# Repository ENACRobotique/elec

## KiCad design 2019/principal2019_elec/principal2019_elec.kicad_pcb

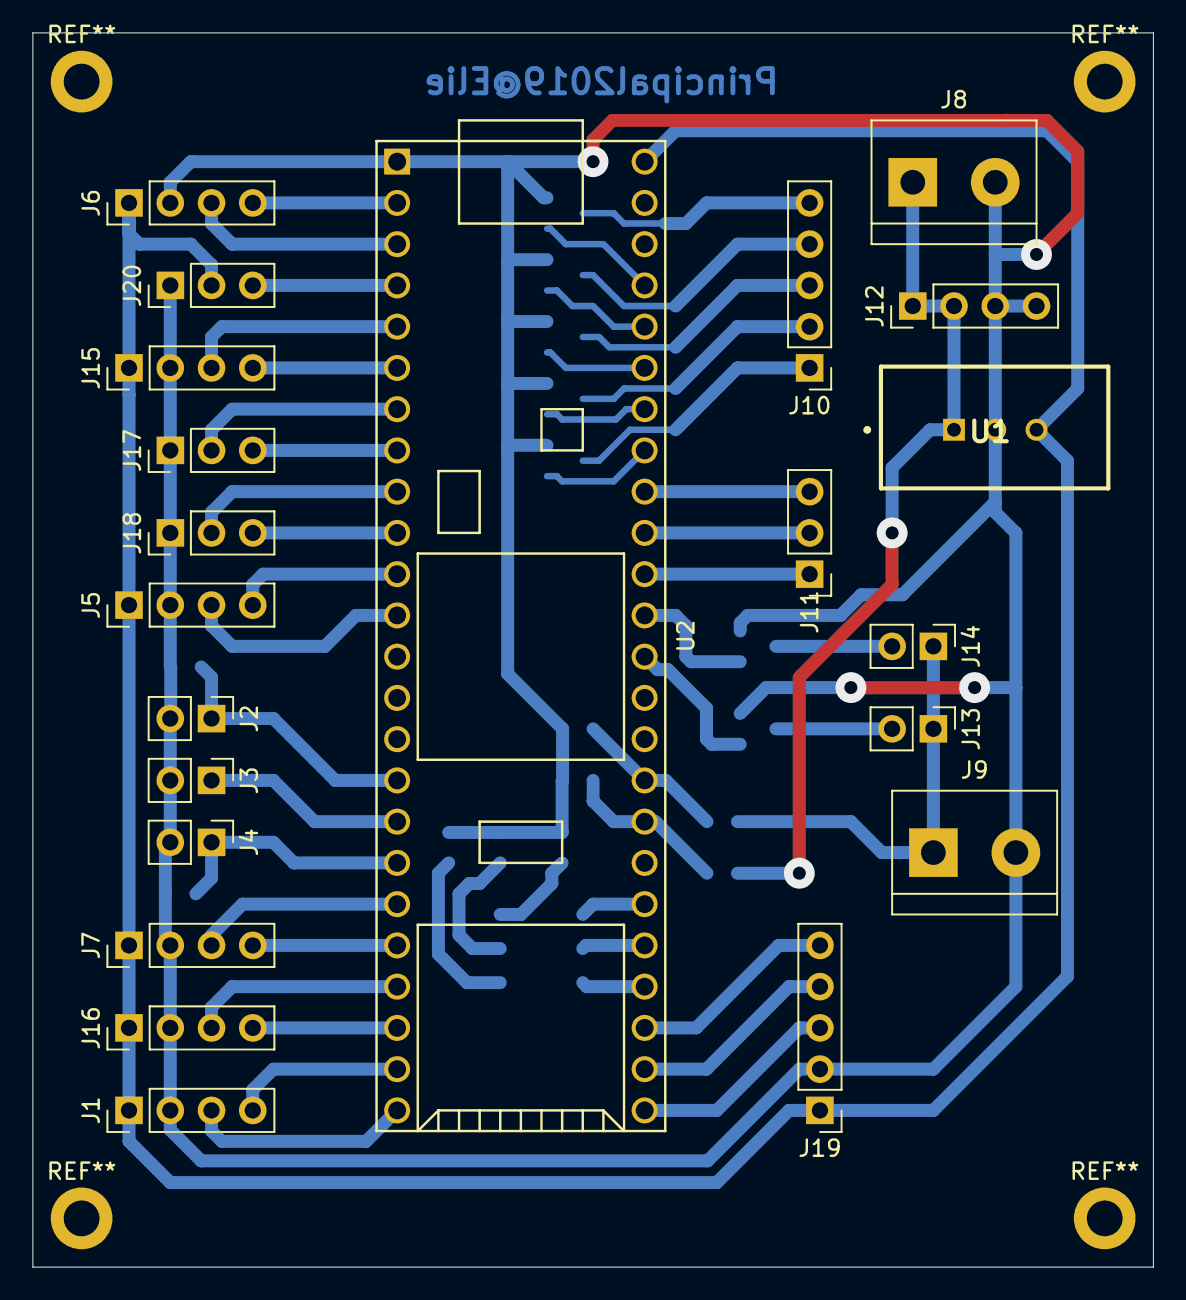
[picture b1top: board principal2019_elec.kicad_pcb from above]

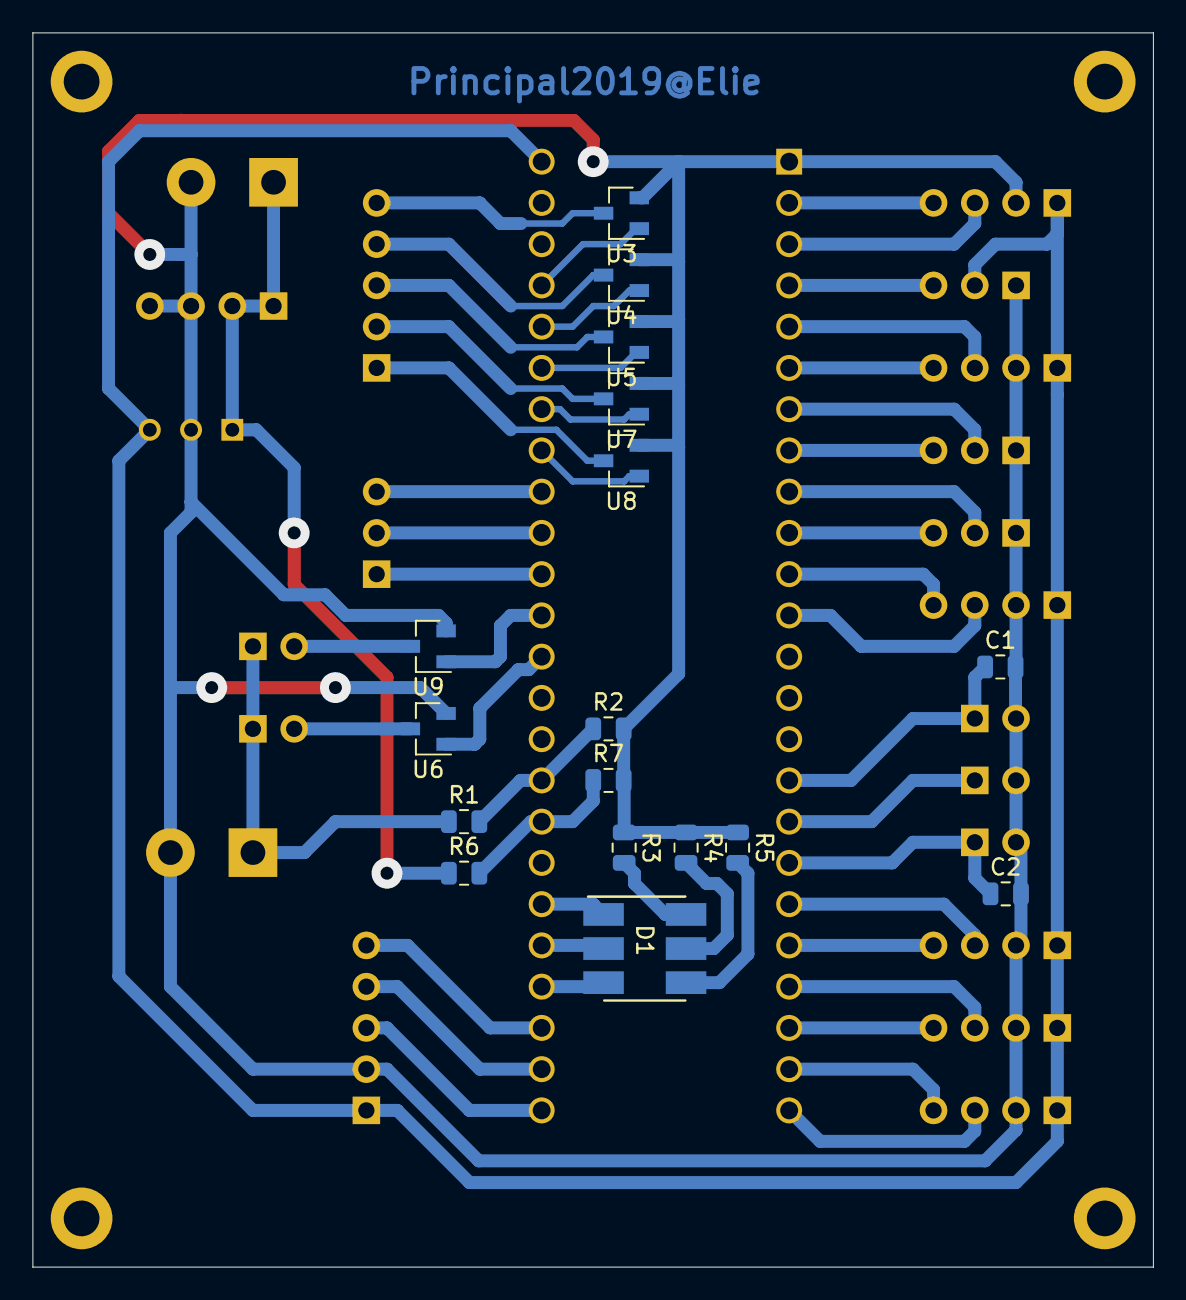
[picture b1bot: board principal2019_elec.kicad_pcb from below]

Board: 2 copper layers, 69.0 x 76.0 mm, 39 parts (17 on the bottom side), 52 nets.

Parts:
C1, C2: 100n; C_0805_2012Metric
D1: LED; PLCC6_CLP6C-FKB
J1: UART4; PinHeader_1x04_P2.54mm_Vertical
J2: tirette; PinHeader_1x02_P2.54mm_Vertical
J3: couleur; PinHeader_1x02_P2.54mm_Vertical
J4: selecteur; PinHeader_1x02_P2.54mm_Vertical
J5: UART2; PinHeader_1x04_P2.54mm_Vertical
J6: Raspi; PinHeader_1x04_P2.54mm_Vertical
J7: doigt_display; PinHeader_1x04_P2.54mm_Vertical
J8: conn_bat_sig; TerminalBlock_bornier-2_P5.08mm
J9: conn_bat_pow; TerminalBlock_bornier-2_P5.08mm
J10: Conn_01x05_Male; PinHeader_1x05_P2.54mm_Vertical
J11: lidar_out; PinHeader_1x03_P2.54mm_Vertical
J12: alim_lidar; PinHeader_1x04_P2.54mm_Vertical
J13: vanne; PinHeader_1x02_P2.54mm_Vertical
J14: pompe; PinHeader_1x02_P2.54mm_Vertical
J15: enc_mot1; PinHeader_1x04_P2.54mm_Vertical
J16: enc_mot2; PinHeader_1x04_P2.54mm_Vertical
J17: mot1; PinHeader_1x03_P2.54mm_Vertical
J18: mot2; PinHeader_1x03_P2.54mm_Vertical
J19: dynamixel; PinHeader_1x05_P2.54mm_Vertical
J20: Servo; PinHeader_1x03_P2.54mm_Vertical
R1, R6: 10k; R_0805_2012Metric
R2, R7: 2.2k; R_0805_2012Metric
R3: 68; R_0805_2012Metric
R4, R5: 10; R_0805_2012Metric
U1: regu_5V; TSR-2
U2: Teensy3.5; Teensy35_36
U3: mosfet_lid_I1; SOT-23
U4: mosfet_lid_I2; SOT-23
U5: mosfet_lid_I3; SOT-23
U6: mosfet_vanne; SOT-23
U7: mosfet_lid_I4; SOT-23
U8: mosfet_lid_I5; SOT-23
U9: mosfet_pompe; SOT-23

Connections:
+5V: J1.1, J5.1, J6.1, J7.1, J15.1, J16.1, J19.1, J20.2, U1.3, U2.53
+12P: J9.1, J13.1, J14.1, R1.1
+12V: J8.1, J12.1, J12.2, R6.1, U1.1
/CLK: J7.4, U2.20
/DIO: J7.3, U2.19
/RW_dyn: J19.5, U2.32
/Rx2: J5.4, U2.11
/Rx4: J1.4, U2.23
/Rx_dyn: J19.4, U2.31
/Rx_raspi: J6.4, U2.2
/Tx2: J5.3, U2.12
/Tx4: J1.3, U2.24
/Tx_dyn: J19.3, U2.30
/Tx_raspi: J6.3, U2.3
/Vpower: R1.2, R2.1, U2.38
/Vsignal: R6.2, R7.1, U2.37
/couleur: J3.1, U2.17
/enc1_A: J15.3, U2.5
/enc1_B: J15.4, U2.6
/enc2_A: J16.3, U2.21
/enc2_B: J16.4, U2.22
/led_B: D1.3, U2.33
/led_G: D1.2, U2.34
/led_R: D1.1, U2.35
/lidar_I1: U2.50, U3.1
/lidar_I2: U2.49, U4.1
/lidar_I3: U2.48, U5.1
/lidar_I4: U2.47, U7.1
/lidar_I5: U2.46, U8.1
/lidar_out1: J11.1, U2.43
/lidar_out2: J11.2, U2.44
/lidar_out3: J11.3, U2.45
/mot1_PWM: J17.2, U2.7
/mot1_dir: J17.3, U2.8
/mot2_PWM: J18.2, U2.9
/mot2_dir: J18.3, U2.10
/pompe: U2.42, U9.1
/selecteur: C2.1, J4.1, U2.18
/servo: J20.3, U2.4
/tirette: C1.1, J2.1, U2.16
/vanne: U2.41, U6.1
GND: C1.2, C2.2, J1.2, J2.2, J3.2, J4.2, J5.2, J6.2, J7.2, J8.2, J9.2, J12.3, J12.4, J15.2, J16.2, J17.1, J18.1, J19.2, J20.1, R2.2, R3.1, R4.1, R5.1, R7.2, U1.2, U2.1, U3.2, U4.2, U5.2, U6.2, U7.2, U8.2, U9.2
unnamed: D1.4, R5.2
unnamed: D1.5, R4.2
unnamed: D1.6, R3.2
unnamed: J10.1, U8.3
unnamed: J10.2, U7.3
unnamed: J10.3, U5.3
unnamed: J10.4, U4.3
unnamed: J10.5, U3.3
unnamed: J13.2, U6.3
unnamed: J14.2, U9.3

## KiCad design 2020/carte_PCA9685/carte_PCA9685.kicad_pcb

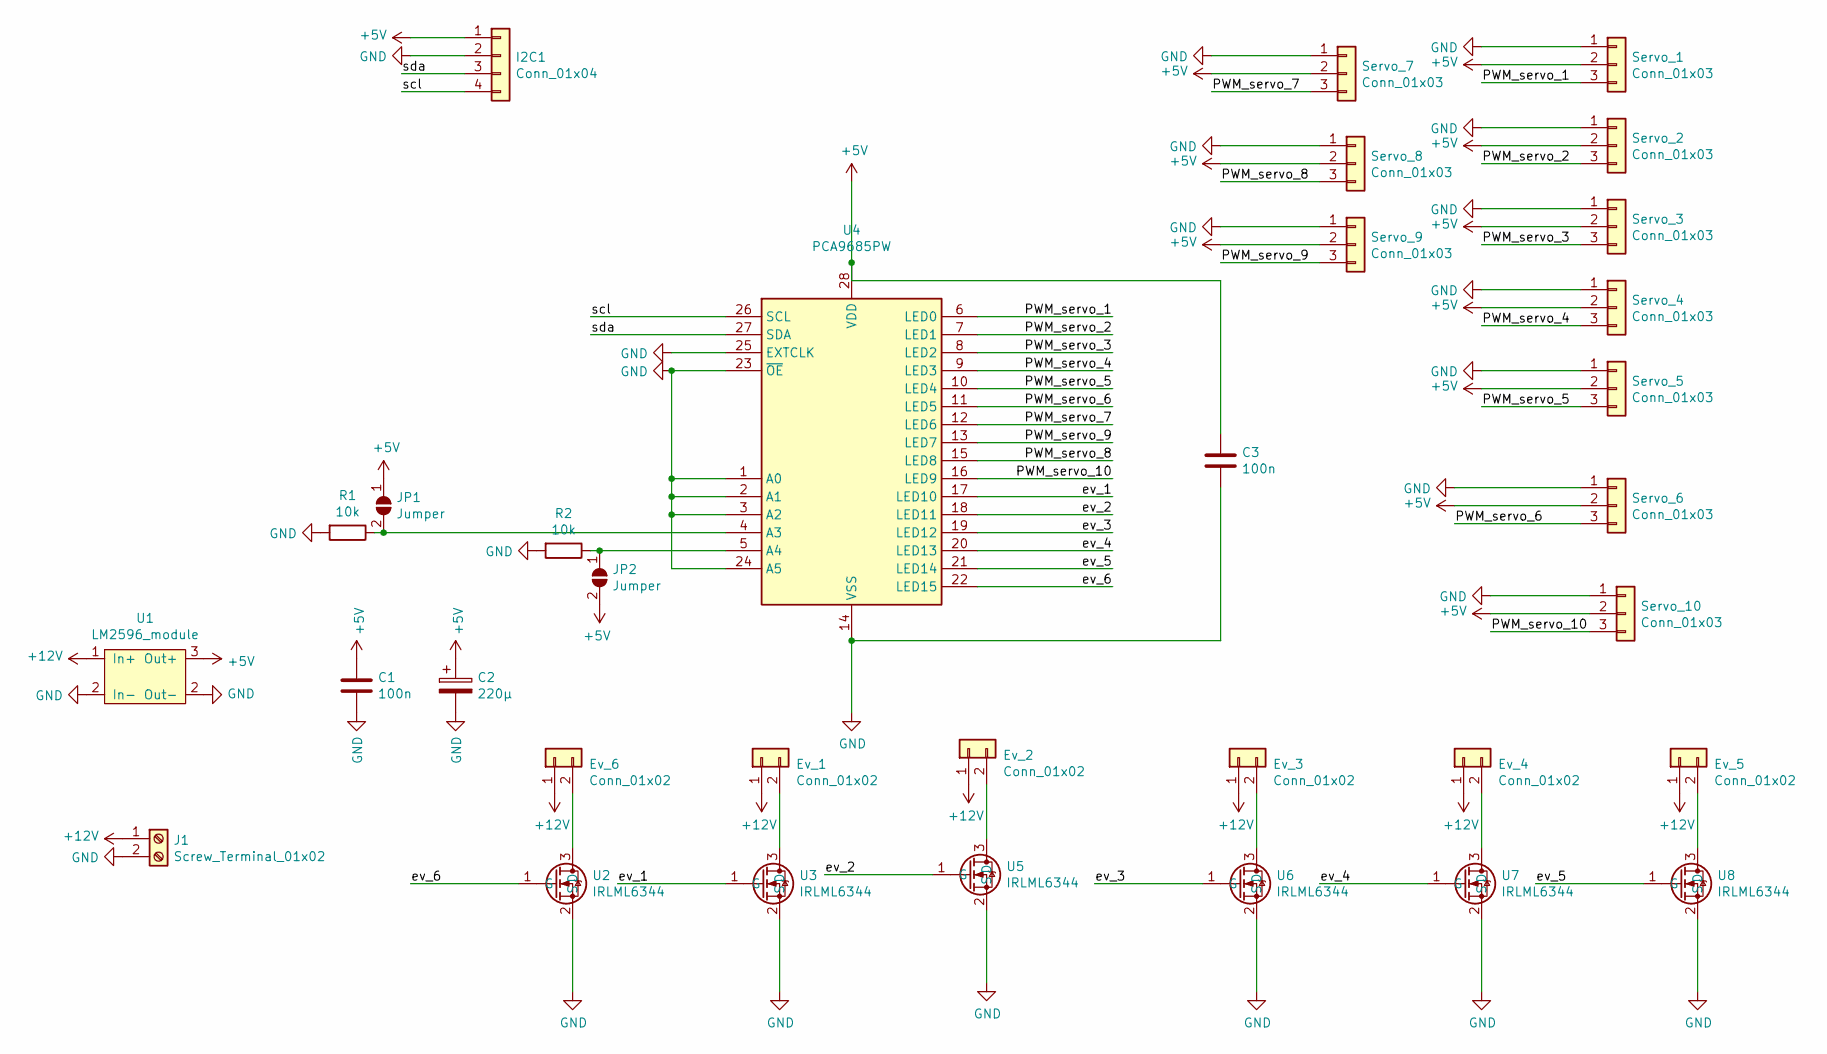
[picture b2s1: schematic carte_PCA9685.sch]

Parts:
C1, C3: 100n; C_0603_1608Metric_Pad1.05x0.95mm_HandSolder
C2: 220µ; CP_Radial_D10.0mm_P7.50mm
Ev_1, Ev_2, Ev_3, Ev_4, Ev_5, Ev_6: Conn_01x02; JST_XH_B2B-XH-A_1x02_P2.50mm_Vertical
I2C1: Conn_01x04; JST_XH_B4B-XH-A_1x04_P2.50mm_Vertical
J1: Screw_Terminal_01x02; TerminalBlock_4Ucon_1x02_P3.50mm_Vertical
JP1, JP2: Jumper; SolderJumper-2_P1.3mm_Open_TrianglePad1.0x1.5mm
R1, R2: 10k; R_0805_2012Metric
Servo_1, Servo_2, Servo_3, Servo_4, Servo_5, Servo_6, Servo_7, Servo_8, Servo_9, Servo_10: Conn_01x03; PinHeader_1x03_P2.54mm_Vertical
U1: LM2596_module
U2, U3, U5, U6, U7, U8: IRLML6344; SOT-23
U4: PCA9685PW; TSSOP-28_4.4x9.7mm_P0.65mm

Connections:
+5V: C1.2, C2.1, C3.1, I2C1.1, JP1.1 (A), JP2.2 (B), Servo_1.2, Servo_2.2, Servo_3.2, Servo_4.2, Servo_5.2, Servo_6.2, Servo_7.2, Servo_8.2, Servo_9.2, Servo_10.2, U1.3 (Out+), U4.28 (VDD)
+12V: Ev_1.1, Ev_2.1, Ev_3.1, Ev_4.1, Ev_5.1, Ev_6.1, J1.1, U1.1 (In+)
/PWM_servo_1: Servo_1.3, U4.6 (LED0)
/PWM_servo_2: Servo_2.3, U4.7 (LED1)
/PWM_servo_3: Servo_3.3, U4.8 (LED2)
/PWM_servo_4: Servo_4.3, U4.9 (LED3)
/PWM_servo_5: Servo_5.3, U4.10 (LED4)
/PWM_servo_6: Servo_6.3, U4.11 (LED5)
/PWM_servo_7: Servo_7.3, U4.12 (LED6)
/PWM_servo_8: Servo_8.3, U4.15 (LED8)
/PWM_servo_9: Servo_9.3, U4.13 (LED7)
/PWM_servo_10: Servo_10.3, U4.16 (LED9)
/ev_1: U3.1 (G), U4.17 (LED10)
/ev_2: U4.18 (LED11), U5.1 (G)
/ev_3: U4.19 (LED12), U6.1 (G)
/ev_4: U4.20 (LED13), U7.1 (G)
/ev_5: U4.21 (LED14), U8.1 (G)
/ev_6: U2.1 (G), U4.22 (LED15)
/scl: I2C1.4, U4.26 (SCL)
/sda: I2C1.3, U4.27 (SDA)
GND: C1.1, C2.2, C3.2, I2C1.2, J1.2, R1.2, R2.2, Servo_1.1, Servo_2.1, Servo_3.1, Servo_4.1, Servo_5.1, Servo_6.1, Servo_7.1, Servo_8.1, Servo_9.1, Servo_10.1, U1.2 (In-), U2.2 (S), U3.2 (S), U4.1 (A0), U4.2 (A1), U4.3 (A2), U4.14 (VSS), U4.23 (~OE), U4.24 (A5), U4.25 (EXTCLK), U5.2 (S), U6.2 (S), U7.2 (S), U8.2 (S)
unnamed: Ev_1.2, U3.3 (D)
unnamed: Ev_2.2, U5.3 (D)
unnamed: Ev_3.2, U6.3 (D)
unnamed: Ev_4.2, U7.3 (D)
unnamed: Ev_5.2, U8.3 (D)
unnamed: Ev_6.2, U2.3 (D)
unnamed: JP1.2 (B), R1.1, U4.4 (A3)
unnamed: JP2.1 (A), R2.1, U4.5 (A4)

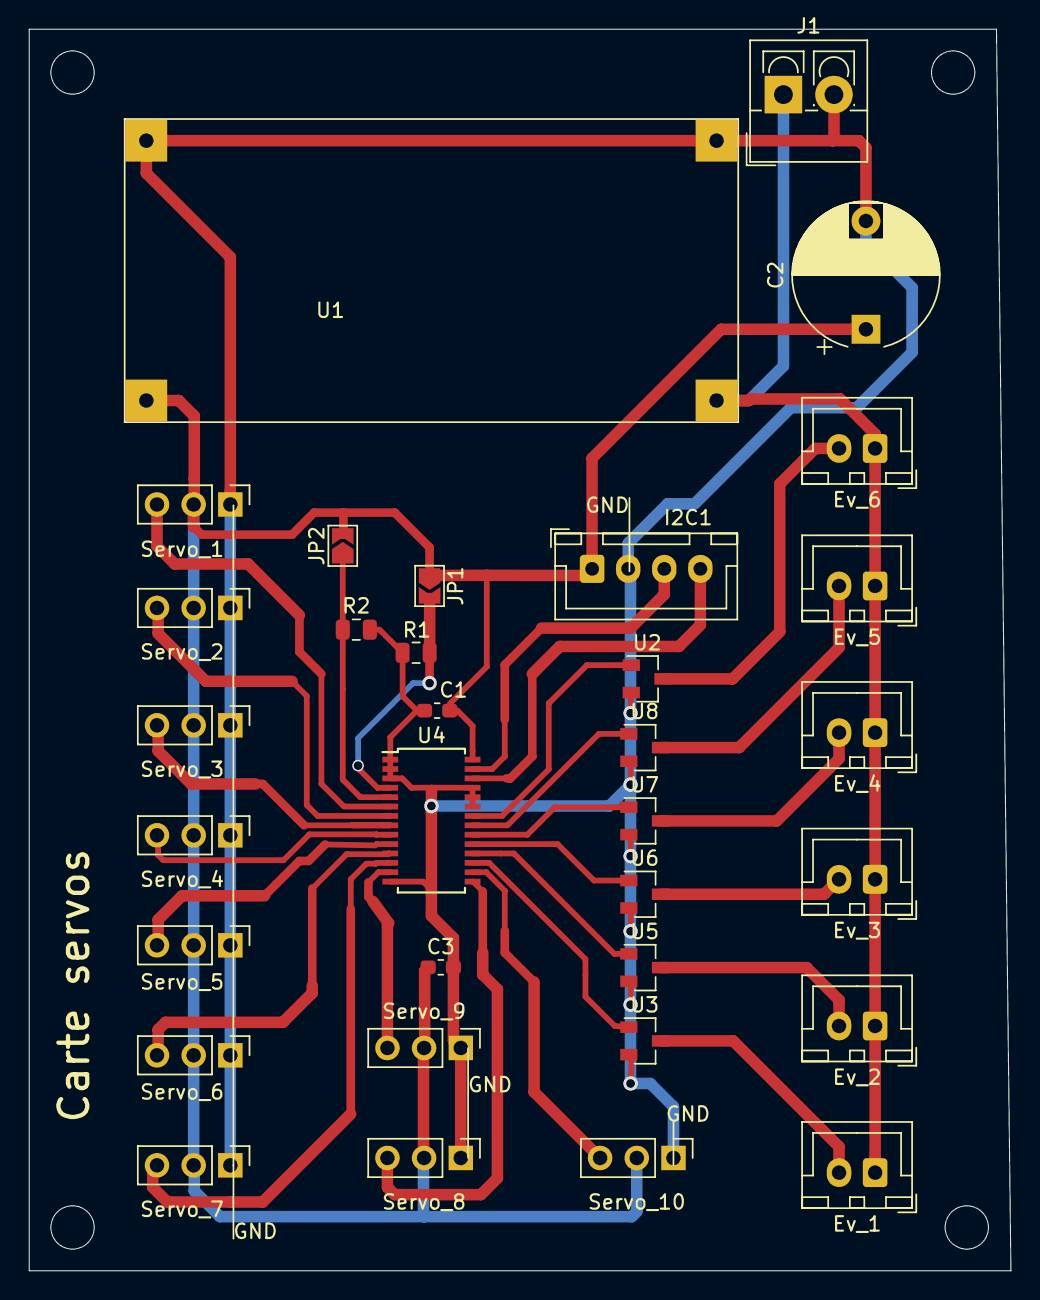
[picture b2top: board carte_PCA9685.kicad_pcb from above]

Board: 2 copper layers, 68.0 x 86.0 mm, 37 parts (0 on the bottom side), 29 nets.

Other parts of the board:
 : MountingHole_3mm
 #2,  #3,  #4: MountingHole_3mm

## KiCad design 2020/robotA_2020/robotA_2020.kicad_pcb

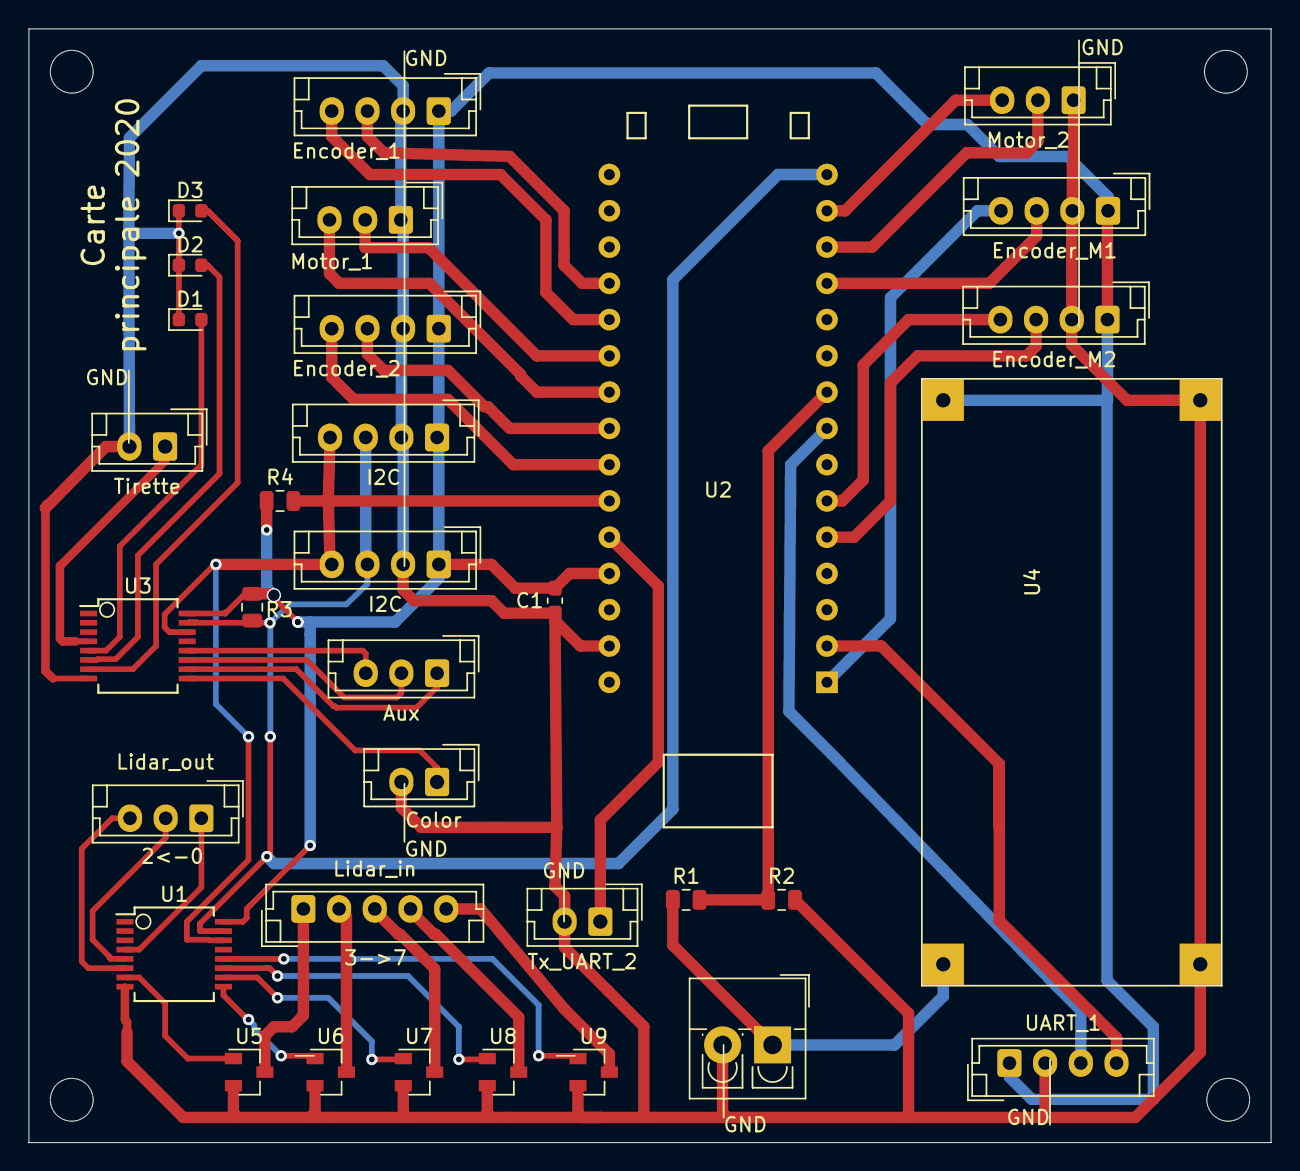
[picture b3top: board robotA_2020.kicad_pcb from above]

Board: 2 copper layers, 87.0 x 78.0 mm, 37 parts (0 on the bottom side), 42 nets.

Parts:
 : Screw_Terminal_01x02; TerminalBlock_4Ucon_1x02_P3.50mm_Vertical
 #2,  #3,  #4,  #5: MountingHole_3mm
Aux: Conn_01x03; JST_EH_B3B-EH-A_1x03_P2.50mm_Vertical
C1: 100nF; C_0603_1608Metric_Pad1.05x0.95mm_HandSolder
Color: Conn_01x02; JST_EH_B2B-EH-A_1x02_P2.50mm_Vertical
D1, D2, D3: LED; LED_0603_1608Metric
Encoder_1: Encoder_1; JST_EH_B4B-EH-A_1x04_P2.50mm_Vertical
Encoder_2: Encoder_2; JST_EH_B4B-EH-A_1x04_P2.50mm_Vertical
Encoder_M1: Encoder_M1; JST_EH_B4B-EH-A_1x04_P2.50mm_Vertical
Encoder_M2: Encoder_M2; JST_EH_B4B-EH-A_1x04_P2.50mm_Vertical
I2C, I2C#2: I2C_3; JST_EH_B4B-EH-A_1x04_P2.50mm_Vertical
Lidar_in: Conn_01x05; JST_EH_B5B-EH-A_1x05_P2.50mm_Vertical
Lidar_out: Conn_01x03; JST_EH_B3B-EH-A_1x03_P2.50mm_Vertical
Motor_1: Motor_1; JST_EH_B3B-EH-A_1x03_P2.50mm_Vertical
Motor_2: Motor_2; JST_EH_B3B-EH-A_1x03_P2.50mm_Vertical
R1: 4.7k; R_0805_2012Metric
R2: 1k; R_0805_2012Metric
R3, R4: 2.2k; R_0805_2012Metric
Tirette: Conn_01x02; JST_EH_B2B-EH-A_1x02_P2.50mm_Vertical
Tx_UART_2: Conn_01x02; JST_EH_B2B-EH-A_1x02_P2.50mm_Vertical
U1, U3: PCA9554D; SSOP-16_5.3x6.2mm_P0.65mm
U2: NUCLEO32-L432KC; NUCLEO32
U4: LM2596_module
U5, U6, U7, U8, U9: IRLML6344; SOT-23
UART_1: UART_1; JST_EH_B4B-EH-A_1x04_P2.50mm_Vertical

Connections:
+5V: C1.2, Encoder_1.1, Encoder_2.1, Encoder_M1.1, Encoder_M2.1, I2C.1, I2C#2.1, R3.1, R4.1, U1.16, U2.27, U3.16, U4.3, UART_1.1
+12V: .1, R1.1, U4.1
/Enc_1A: Encoder_1.3, U2.19
/Enc_1B: Encoder_1.4, U2.20
/Enc_2A: Encoder_2.3, U2.23
/Enc_2B: Encoder_2.4, U2.24
/Enc_M1A: Encoder_M1.3, U2.12
/Enc_M1B: Encoder_M1.4, U2.1
/Enc_M2A: Encoder_M2.3, U2.5
/Enc_M2B: Encoder_M2.4, U2.6
/Rx_UART_1: U2.2, UART_1.4
/SCL_I2C_3: I2C.4, I2C#2.4, R4.2, U1.14, U2.25, U3.14
/SDA_I2C_3: I2C.3, I2C#2.3, R3.2, U1.15, U2.15, U3.15
/Tx_UART_1: U2.8, UART_1.3
/Tx_UART_2: Tx_UART_2.1, U2.26
/aux_1: Aux.1, U3.10
/aux_2: Aux.2, U3.11
/aux_3: Aux.3, U3.12
/bat_meas: R1.2, R2.1, U2.9
/color: Color.1, U3.9
/led_1: D1.2, U3.5
/led_2: D2.2, U3.6
/led_3: D3.2, U3.7
/lidar_in_1: U1.7, U5.1
/lidar_in_2: U1.9, U6.1
/lidar_in_3: U1.10, U7.1
/lidar_in_4: U1.11, U8.1
/lidar_in_5: U1.12, U9.1
/lidar_out_1: Lidar_out.1, U1.4
/lidar_out_2: Lidar_out.2, U1.5
/lidar_out_3: Lidar_out.3, U1.6
/mot_1_DIR: Motor_1.3, U2.22
/mot_1_PWM: Motor_1.2, U2.21
/mot_2_DIR: Motor_2.3, U2.14
/mot_2_PWM: Motor_2.2, U2.13
/tirette: Tirette.1, U3.4
GND: .2, C1.1, Color.2, D1.1, D2.1, D3.1, Encoder_1.2, Encoder_2.2, Encoder_M1.2, Encoder_M2.2, I2C.2, I2C#2.2, Motor_1.1, Motor_2.1, R2.2, Tirette.2, Tx_UART_2.2, U1.8, U2.29, U3.8, U4.2, U5.2, U6.2, U7.2, U8.2, U9.2, UART_1.2
unnamed: Lidar_in.1, U5.3
unnamed: Lidar_in.2, U6.3
unnamed: Lidar_in.3, U7.3
unnamed: Lidar_in.4, U8.3
unnamed: Lidar_in.5, U9.3

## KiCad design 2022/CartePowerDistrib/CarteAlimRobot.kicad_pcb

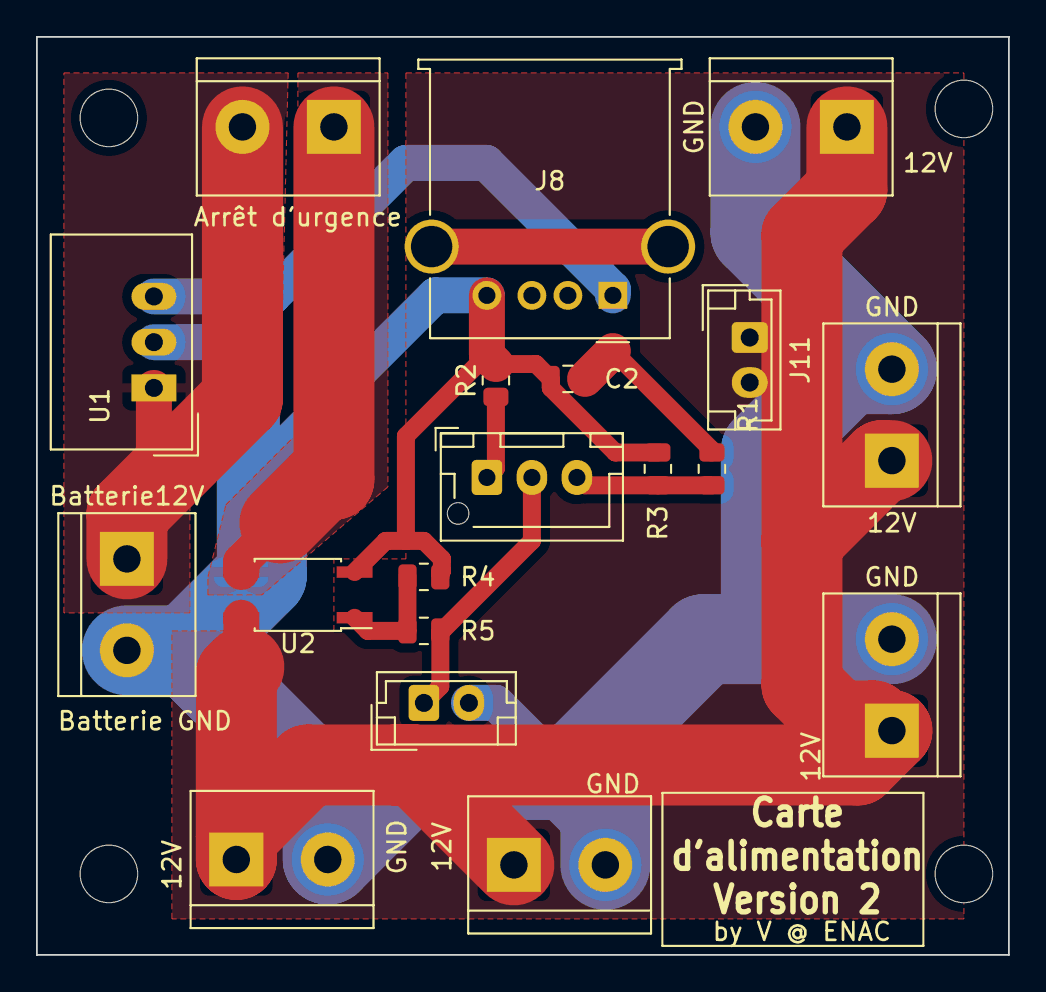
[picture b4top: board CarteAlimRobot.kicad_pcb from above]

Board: 2 copper layers, 54.0 x 51.0 mm, 19 parts (0 on the bottom side), 10 nets.

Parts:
C2: C; C_0805_2012Metric
J1, J2, J3, J4, J5, J6, J7: Screw_Terminal_01x02; TerminalBlock_bornier-2_P5.08mm
J8: USB_A; USB_A_Molex_67643_Horizontal
J9: Conn_01x03_Male; JST_XH_B3B-XH-AM_1x03_P2.50mm_Vertical
J10, J11: Conn_01x02_Male; JST_EH_B2B-EH-A_1x02_P2.50mm_Vertical
R1, R2, R3, R4, R5: R; R_0805_2012Metric
U1: TSR_1-2450; Converter_DCDC_TRACO_TSR-1_THT
U2: ASSR-1218; SO-4_4.4x3.6mm_P2.54mm

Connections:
12V_P: J3.1, J4.1, J5.1, J6.1, J7.1, U2.4
+5V: C2.1, J11.2, R1.2, U1.3 (Vout)
+12V: J1.2, J2.1, U1.1 (Vin)
GND: C2.2, J2.2, J3.2, J4.2, J5.2, J6.2, J7.2, J8.4 (GND), J10.2, R2.2, R3.1, R4.1, U1.2 (GND), U2.2
unnamed: J1.1, U2.3
unnamed: J8.1 (VBUS), J11.1
unnamed: J9.1, R2.1
unnamed: J9.3, R1.1, R3.2
unnamed: R4.2, R5.2, U2.1
SignalPowerOn: J9.2, J10.1, R5.1

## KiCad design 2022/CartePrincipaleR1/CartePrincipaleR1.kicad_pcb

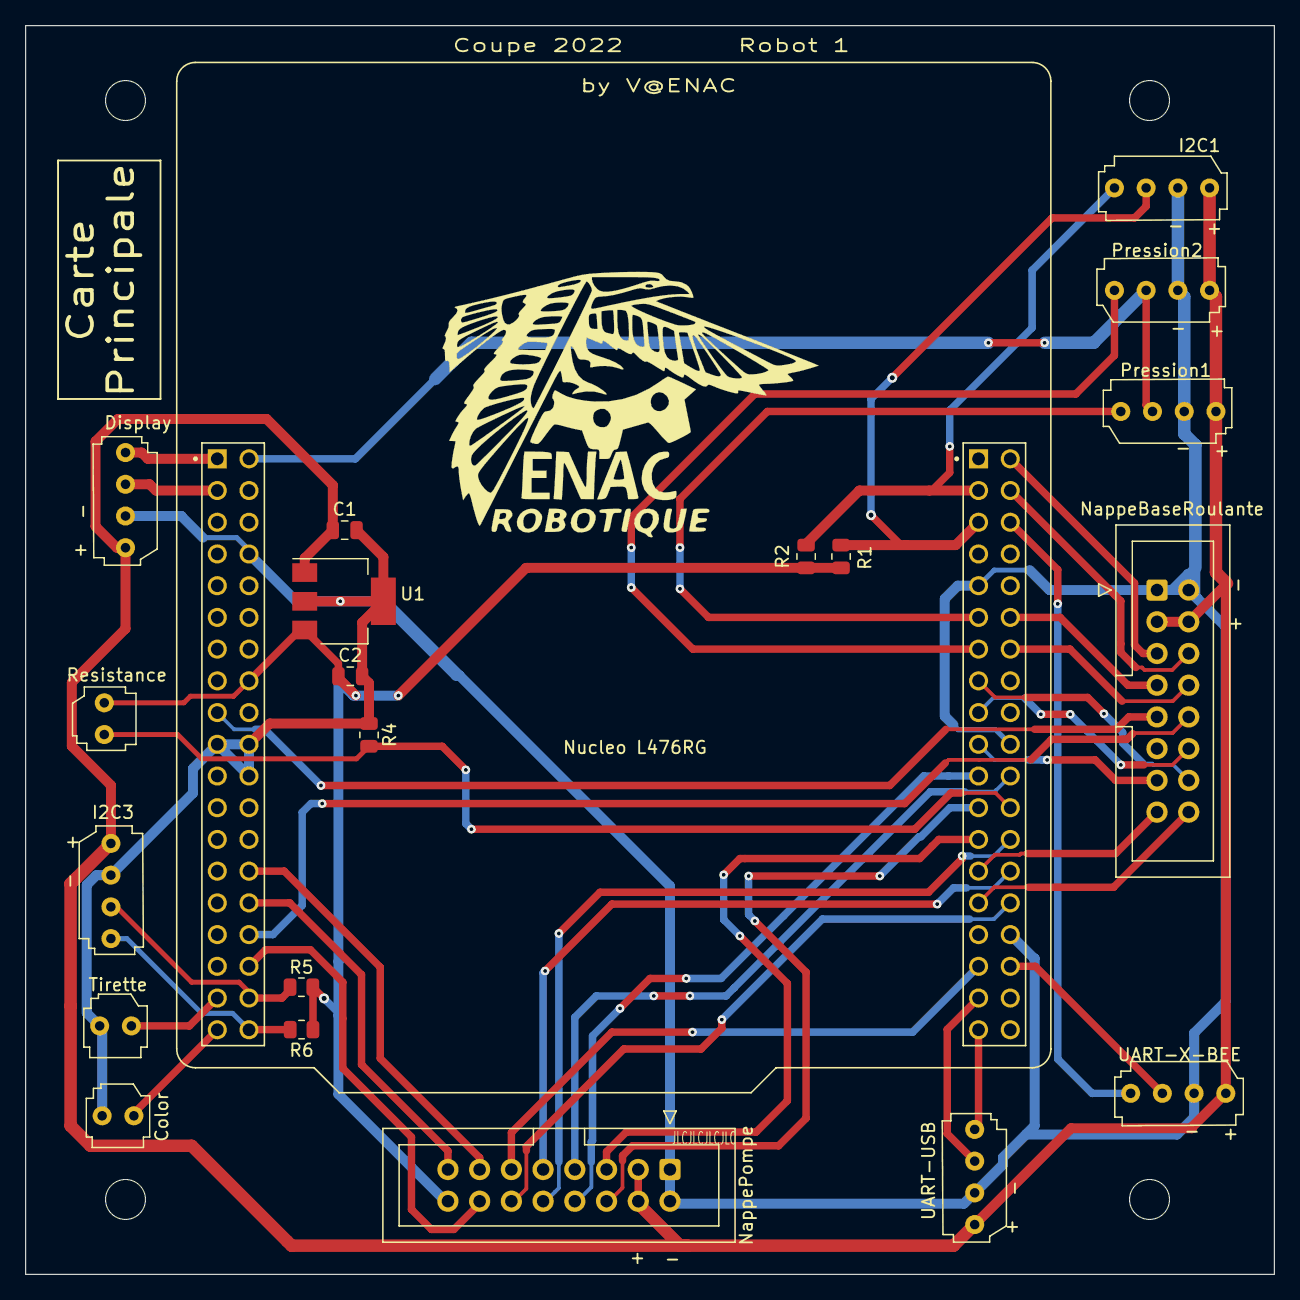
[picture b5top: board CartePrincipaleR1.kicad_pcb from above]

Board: 2 copper layers, 100.0 x 100.0 mm, 21 parts (0 on the bottom side), 41 nets.

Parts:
C1: 100n; C_0805_2012Metric
C2: 10u; C_0805_2012Metric
Color: Conn_01x02_Male; HE14_EMBASE_1x02
Display: Conn_01x04_Male; HE14_EMBASE_1x04
I2C1, I2C3: I2C; HE14_EMBASE_1x04
NappeBaseRoulante: Conn_02x08_Top_Bottom; IDC-Header_2x08_P2.54mm_Vertical
NappePompe: Conn_02x08_Top_Bottom; IDC-Header_2x08_P2.54mm_Vertical
Nucleo L476RG: NUCLEO64-F411RE; ST_NUCLEO-F401RE
Pression1, Pression2: Conn_01x04_Male; HE14_EMBASE_1x04
R1, R2, R5, R6: 2.2k; R_0805_2012Metric
R4: 1k; R_0805_2012Metric
Resistance: Conn_01x02_Male; HE14_EMBASE_1x02
Tirette: Conn_01x02_Male; HE14_EMBASE_1x02
U1: LT1129-3.3_SOT223; SOT-223-3_TabPin2
UART-USB: UART; HE14_EMBASE_1x04
UART-X-BEE: UART; HE14_EMBASE_1x04

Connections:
+3V3: C2.1, NappePompe.16, Nucleo L476RG.16 (+3V3), R1.1, R2.1, R5.1, R6.1, Resistance.1, U1.3 (VO)
+5V: C1.1, Display.1, I2C1.1, I2C3.1, NappeBaseRoulante.3, NappeBaseRoulante.4, NappePompe.3, NappePompe.4, Pression1.4, Pression2.4, U1.1 (VI), UART-USB.1, UART-X-BEE.1
A_Resistance: Nucleo L476RG.62 (PB1), R4.2, Resistance.2
CLK_Display: Display.4, Nucleo L476RG.1 (PC10)
CLK_PRESS: Nucleo L476RG.2 (PC11), Pression1.2, Pression2.2
COL_GPIO: Color.1, Nucleo L476RG.37 (PC3)
CONTACTEUR1_GPIO: NappeBaseRoulante.9, Nucleo L476RG.17 (PA15)
CONTACTEUR2_GPIO: NappeBaseRoulante.10, Nucleo L476RG.32 (PA4)
DATA_PRESS_1: Nucleo L476RG.49 (PA5), Pression1.1
DATA_PRESS_2: Nucleo L476RG.51 (PA6), Pression2.1
DIO_Display: Display.3, Nucleo L476RG.3 (PC12)
DataAX12_TX: NappeBaseRoulante.12, Nucleo L476RG.55 (PB6)
EV1: NappePompe.12, Nucleo L476RG.68 (PB13)
EV2: NappePompe.11, Nucleo L476RG.71 (PA10)
GND: C1.2, C2.2, Color.2, Display.2, I2C1.2, I2C3.2, NappeBaseRoulante.1, NappeBaseRoulante.2, NappePompe.1, NappePompe.2, Nucleo L476RG.8 (GND), Nucleo L476RG.19 (GND), Nucleo L476RG.20 (GND), Nucleo L476RG.22 (GND), Nucleo L476RG.47 (GND), Nucleo L476RG.58 (GND), Nucleo L476RG.70 (AGND), Pression1.3, Pression2.3, R4.1, Tirette.2, U1.2 (GND), UART-USB.2, UART-X-BEE.2
MC1A: NappeBaseRoulante.6, Nucleo L476RG.42 (PC6)
MC1B: NappeBaseRoulante.5, Nucleo L476RG.40 (PC8)
MC2A: NappeBaseRoulante.8, Nucleo L476RG.52 (PA11)
MC2B: NappeBaseRoulante.7, Nucleo L476RG.50 (PA12)
Mot1DIR: NappePompe.7, Nucleo L476RG.60 (PB2)
Mot1PWM: NappePompe.8, Nucleo L476RG.59 (PA9)
Mot2DIR: NappePompe.5, Nucleo L476RG.63 (PB10)
Mot2PWM: NappePompe.6, Nucleo L476RG.61 (PA8)
POMPE1: NappePompe.9, Nucleo L476RG.66 (PB14)
POMPE2: NappePompe.10, Nucleo L476RG.64 (PB15)
RC_1A: NappeBaseRoulante.16, Nucleo L476RG.67 (PB5)
RC_1B: NappeBaseRoulante.15, Nucleo L476RG.65 (PB4)
RC_2A: NappeBaseRoulante.14, Nucleo L476RG.53 (PA7)
RC_2B: NappeBaseRoulante.13, Nucleo L476RG.57 (PC7)
S1: NappePompe.13, Nucleo L476RG.28 (PA0)
S2: NappePompe.15, Nucleo L476RG.30 (PA1)
S3: NappePompe.14, Nucleo L476RG.34 (PB0)
SCL_I2C1: I2C1.4, Nucleo L476RG.41 (PB8), R2.2
SCL_I2C3: I2C3.4, Nucleo L476RG.38 (PC0), R6.2
SDA_I2C1: I2C1.3, Nucleo L476RG.43 (PB9), R1.2
SDA_I2C3: I2C3.3, Nucleo L476RG.36 (PC1), R5.2
TIR_GPIO: Nucleo L476RG.35 (PC2), Tirette.1
USART_RX: Nucleo L476RG.75 (STLINK_UART_RX/PA3), UART-USB.4
USART_TX: Nucleo L476RG.73 (STLINK_UART_TX/PA2), UART-USB.3
XBeeTx: Nucleo L476RG.72 (PC4), UART-X-BEE.3
XbeeRx: Nucleo L476RG.44 (PC5), UART-X-BEE.4

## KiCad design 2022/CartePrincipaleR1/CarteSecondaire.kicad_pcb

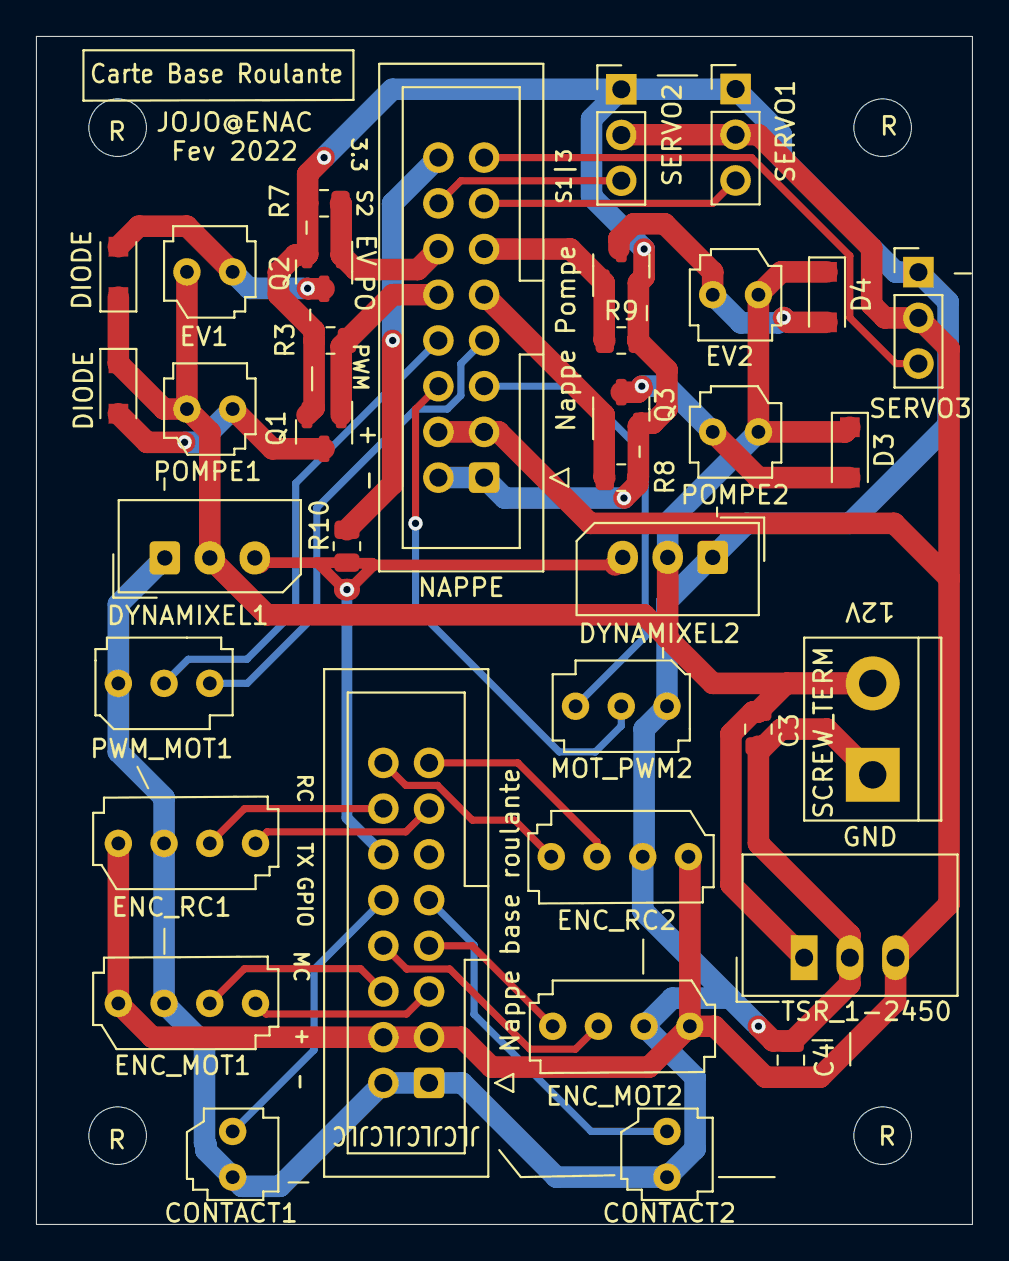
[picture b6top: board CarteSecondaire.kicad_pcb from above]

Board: 2 copper layers, 52.0 x 66.0 mm, 40 parts (0 on the bottom side), 30 nets.

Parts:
C3, C4: C; C_0805_2012Metric
CONTACT1: CONTACT_1; HE14_EMBASE_1x02
CONTACT2: CONTACT_2; HE14_EMBASE_1x02
D3, D4: PMEG2020EH; D_SOD-123F
DIODE: PMEG2020EH; D_SOD-123F
DIODE#2: PMEG2020EH; D_SOD-123F
DYNAMIXEL1: AX12_1; Molex_SPOX_5267-03A_1x03_P2.50mm_Vertical
DYNAMIXEL2: AX12_2; Molex_SPOX_5267-03A_1x03_P2.50mm_Vertical
ENC_MOT1: ENC_MOT_1; HE14_EMBASE_1x04
ENC_MOT2: ENC_MOT_2; HE14_EMBASE_1x04
ENC_RC1: ENC_FOL_1; HE14_EMBASE_1x04
ENC_RC2: ENC_FOL_2; HE14_EMBASE_1x04
EV1: EV1; HE14_EMBASE_1x02
EV2: EV2; HE14_EMBASE_1x02
MOT_PWM2: MOT_PWM_2; HE14_EMBASE_1x03
NAPPE: Conn_02x08_Top_Bottom; IDC-Header_2x08_P2.54mm_Vertical
Nappe Pompe: IRLML0030; SOT-23
Nappe base roulante: Conn_02x08_Top_Bottom; IDC-Header_2x08_P2.54mm_Vertical
POMPE1: POMPE1; HE14_EMBASE_1x02
POMPE2: POMPE2; HE14_EMBASE_1x02
PWM_MOT1: MOT_PWM_1; HE14_EMBASE_1x03
Q1, Q2, Q3: IRLML0030; SOT-23
R: MountingHole_3.2mm_M3
R3, R7, R8, R9: 10k; R_0805_2012Metric
R10: 1k; R_0805_2012Metric
R#2, R#3, R#4: MountingHole_3.2mm_M3
SCREW_TERM: Screw_Terminal_01x02; TerminalBlock_bornier-2_P5.08mm
SERVO1: SERVO1; PinHeader_1x03_P2.54mm_Vertical
SERVO2: SERVO2; PinHeader_1x03_P2.54mm_Vertical
SERVO3: SERVO3; PinHeader_1x03_P2.54mm_Vertical
TSR_1-2450: TSR_1-2450; Converter_DCDC_TRACO_TSR-1_THT

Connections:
+3V3: NAPPE.16, R10.1
+5V: C4.2, ENC_MOT1.1, ENC_MOT2.1, ENC_RC1.1, ENC_RC2.1, NAPPE.3, NAPPE.4, Nappe base roulante.3, Nappe base roulante.4, SERVO1.2, SERVO2.2, SERVO3.2, TSR_1-2450.3 (Vout)
+12V: C3.1, D3.1 (K), D4.1 (K), DIODE.1 (K), DIODE#2.1 (K), DYNAMIXEL1.2, DYNAMIXEL2.2, EV1.1, EV2.1, POMPE1.1, POMPE2.1, SCREW_TERM.2, TSR_1-2450.1 (Vin)
CONTACTEUR1_GPIO: CONTACT1.1, Nappe base roulante.10
CONTACTEUR2_GPIO: CONTACT2.1, Nappe base roulante.9
DataAX12_TX: DYNAMIXEL1.3, DYNAMIXEL2.3, Nappe base roulante.12, R10.2
EV1: NAPPE.12, Q2.1 (G), R7.1
EV2: NAPPE.11, Nappe Pompe.1 (G), R9.1
GND: C3.2, C4.1, CONTACT1.2, CONTACT2.2, DYNAMIXEL1.1, DYNAMIXEL2.1, ENC_MOT1.2, ENC_MOT2.2, ENC_RC1.2, ENC_RC2.2, MOT_PWM2.1, NAPPE.1, NAPPE.2, Nappe Pompe.2 (S), Nappe base roulante.1, Nappe base roulante.2, PWM_MOT1.1, Q1.2 (S), Q2.2 (S), Q3.2 (S), R3.2, R7.2, R8.2, R9.2, SCREW_TERM.1, SERVO1.1, SERVO2.1, SERVO3.1, TSR_1-2450.2 (GND)
MC1A: ENC_MOT1.3, Nappe base roulante.6
MC1B: ENC_MOT1.4, Nappe base roulante.5
MC2A: ENC_MOT2.3, Nappe base roulante.8
MC2B: ENC_MOT2.4, Nappe base roulante.7
Mot1DIR: NAPPE.7, PWM_MOT1.3
Mot1PWM: NAPPE.8, PWM_MOT1.2
Mot2DIR: MOT_PWM2.3, NAPPE.5
Mot2PWM: MOT_PWM2.2, NAPPE.6
unnamed: DIODE.2 (A), POMPE1.2, Q1.3 (D)
unnamed: DIODE#2.2 (A), EV1.2, Q2.3 (D)
unnamed: D3.2 (A), POMPE2.2, Q3.3 (D)
unnamed: D4.2 (A), EV2.2, Nappe Pompe.3 (D)
POMPE1: NAPPE.10, Q1.1 (G), R3.1
POMPE2: NAPPE.9, Q3.1 (G), R8.1
RC_1A: ENC_RC1.3, Nappe base roulante.14
RC_1B: ENC_RC1.4, Nappe base roulante.13
RC_2A: ENC_RC2.3, Nappe base roulante.15
RC_2B: ENC_RC2.4, Nappe base roulante.16
S1: NAPPE.13, SERVO1.3
S2: NAPPE.14, SERVO2.3
S3: NAPPE.15, SERVO3.3

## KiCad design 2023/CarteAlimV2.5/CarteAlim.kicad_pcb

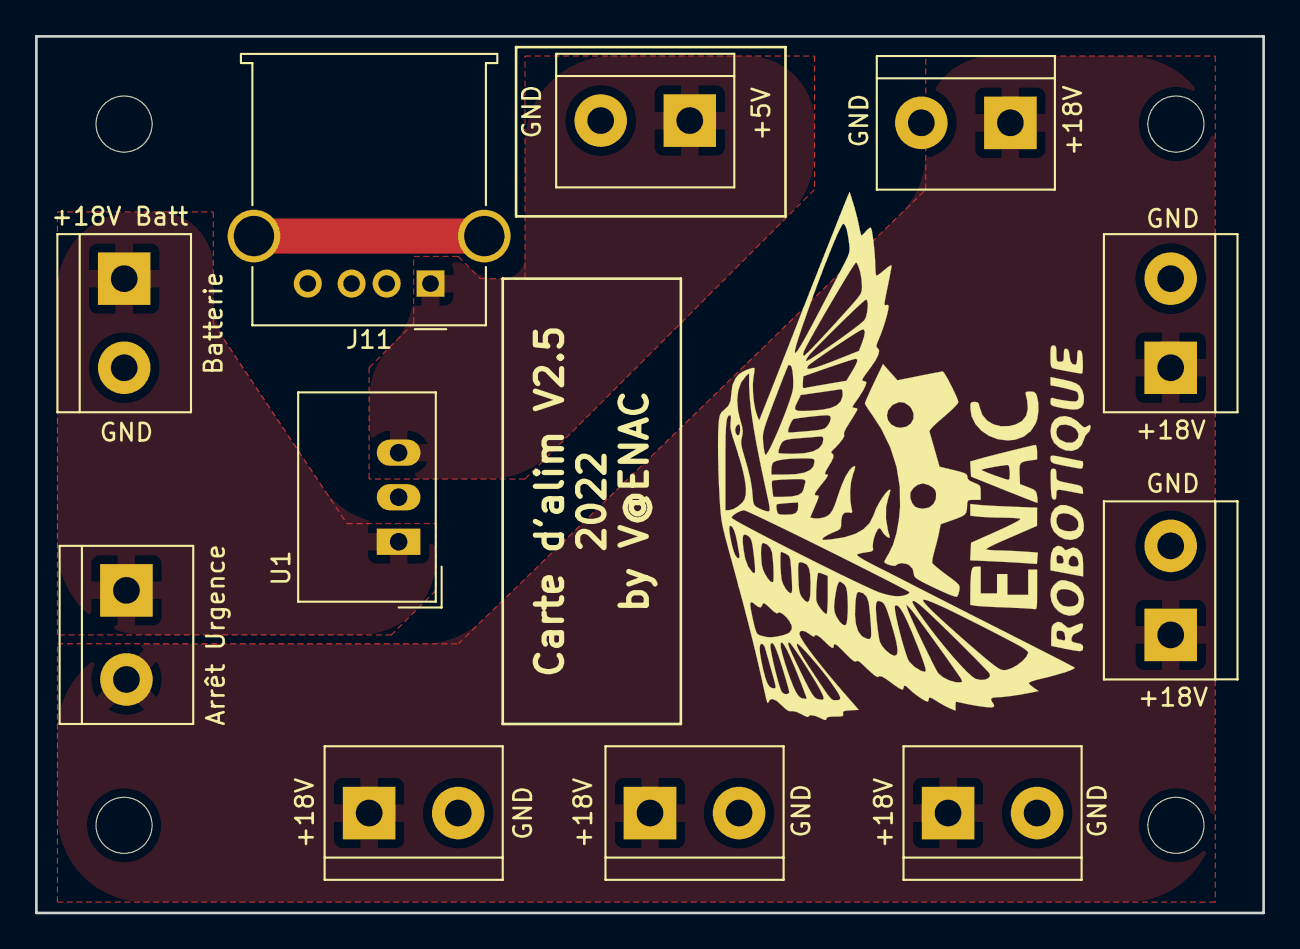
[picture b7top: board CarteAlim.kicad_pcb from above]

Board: 2 copper layers, 70.0 x 50.0 mm, 11 parts (0 on the bottom side), 4 nets.

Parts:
Arrêt Urgence: Screw_Terminal_01x02; TerminalBlock_bornier-2_P5.08mm
Batterie: Screw_Terminal_01x02; TerminalBlock_bornier-2_P5.08mm
J1, J2, J3, J4, J5, J9, J12: Screw_Terminal_01x02; TerminalBlock_bornier-2_P5.08mm
J11: USB_A; USB_A_Molex_67643_Horizontal
U1: TSR_1-2450; Converter_DCDC_TRACO_TSR-1_THT

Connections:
+5V: J11.1 (VBUS), J12.1, U1.3 (Vout)
+18V_Bat: Arrêt Urgence.1, Batterie.1, U1.1 (Vin)
+18V_prot: Arrêt Urgence.2, J1.1, J2.1, J3.1, J4.1, J5.1, J9.1
GND: Batterie.2, J1.2, J2.2, J3.2, J4.2, J5.2, J9.2, J11.4 (GND), J12.2, U1.2 (GND)
